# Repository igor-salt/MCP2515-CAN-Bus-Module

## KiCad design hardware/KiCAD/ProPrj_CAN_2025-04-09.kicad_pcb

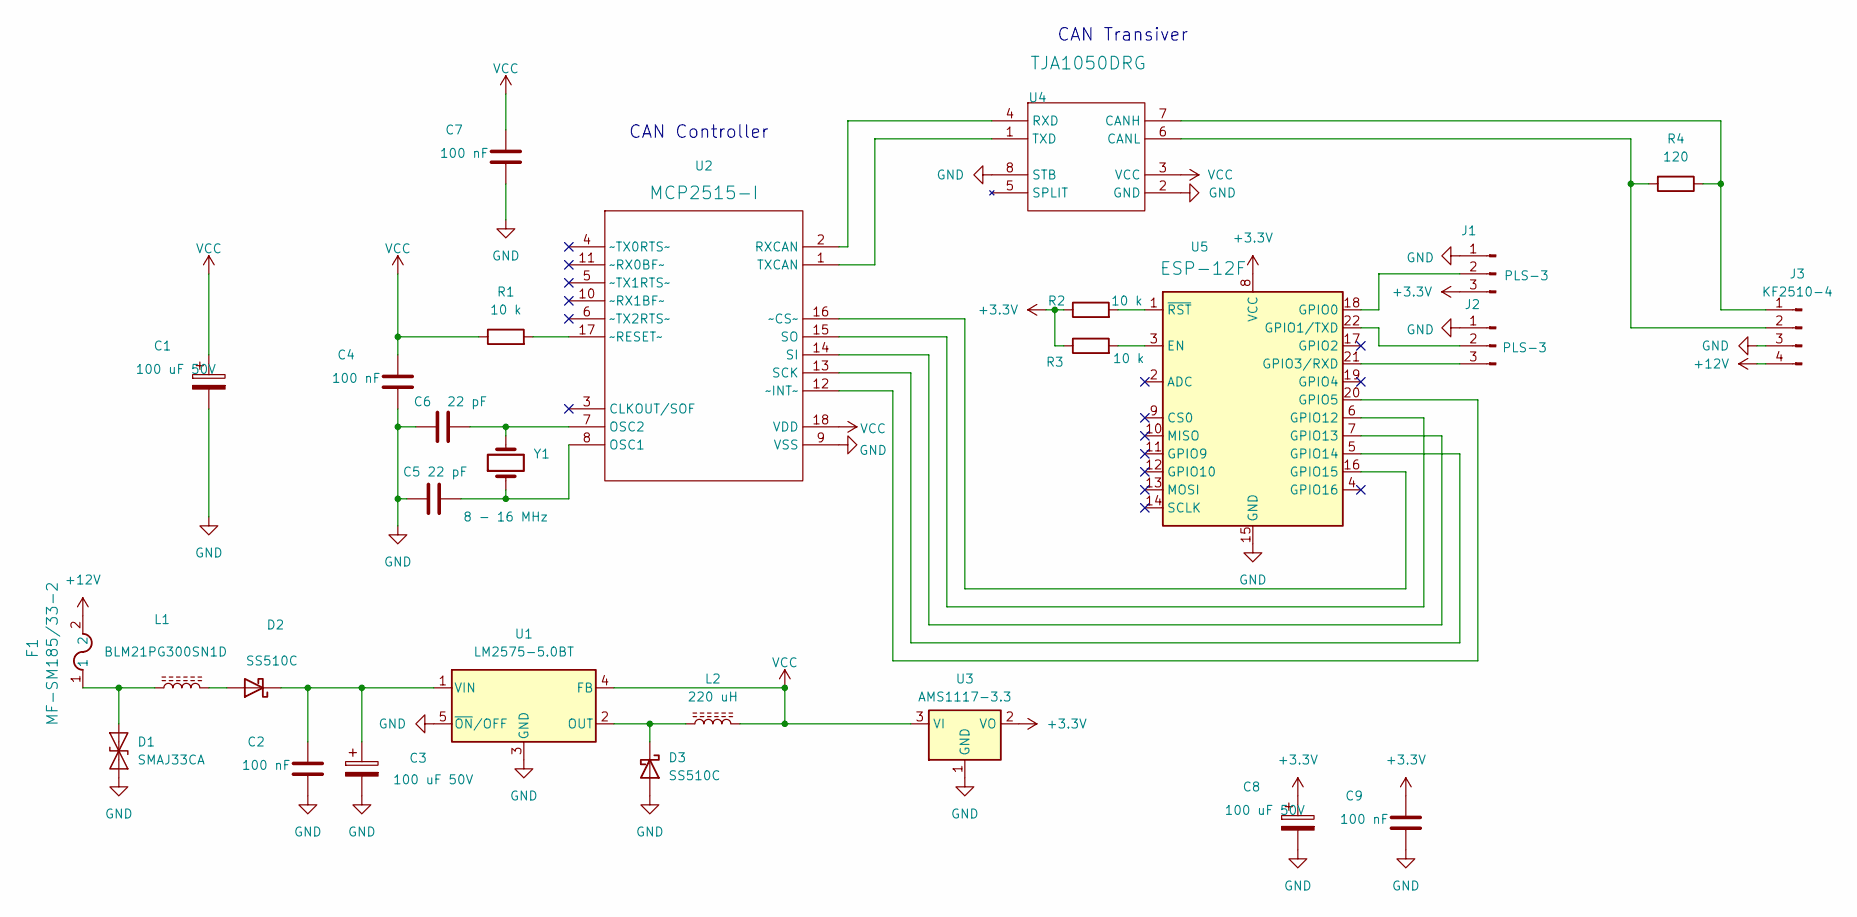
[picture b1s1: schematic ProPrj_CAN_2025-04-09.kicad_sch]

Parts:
C1, C3, C8: 100 uF 50V; C_Elec_8x10.2
C2, C4, C7, C9: 100 nF; C_0603_1608Metric_Pad1.08x0.95mm_HandSolder
C5, C6: 22 pF; C_0603_1608Metric_Pad1.08x0.95mm_HandSolder
D1: SMAJ33CA; D_SMB-SMC_Universal_Handsoldering
D2, D3: SS510C; D_SMB-SMC_Universal_Handsoldering
F1: MF-SM185/33-2; FUSE_MF-SM185_BRN
J1, J2: PLS-3; PinHeader_1x03_P2.54mm_Vertical
J3: KF2510-4; Molex_KK-254_AE-6410-04A_1x04_P2.54mm_Vertical
L1: BLM21PG300SN1D; L_0805_2012Metric_Pad1.05x1.20mm_HandSolder
L2: 220 uH; L_12x12_universal
R1, R2, R3: 10 k; R_0603_1608Metric_Pad0.98x0.95mm_HandSolder
R4: 120; R_0603_1608Metric_Pad0.98x0.95mm_HandSolder
U1: LM2575-5.0BT; TO-263-5_TabPin3
U2: MCP2515-I; SOIC-18_L11.6-W7.5-P1.27-LS10.3-BL; Manufacturer Part MCP2515-I; LCSC Part Name CAN芯片
U3: AMS1117-3.3; SOT-223-3_TabPin2
U4: TJA1050DRG; SOIC-8E; Manufacturer Part TJA1050DRG; LCSC Part Name TJA1050DRG
U5: ESP-12F; ESP-12E
Y1: 8 - 16 MHz; Crystal_SMD_THT_HC49_HandSoldering

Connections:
+3.3V: C8.1, C9.1, J1.3, R2.1, R3.1, U3.2 (VO), U5.8 (VCC)
+12V: F1.2, J3.4
GND: C1.2, C2.2, C3.2, C4.2, C5.1, C6.1, C7.2, C8.2, C9.2, D1.1 (A1), D3.2 (A), J1.1, J2.1, J3.3, U1.3 (GND), U1.5 (~ON/OFF), U2.9 (VSS), U3.1 (GND), U4.2 (GND), U4.8 (STB), U5.15 (GND)
unnamed: D1.2 (A2), F1.1, L1.1
unnamed: D2.2 (A), L1.2
unnamed: C2.1, C3.1, D2.1 (K), U1.1 (VIN)
unnamed: D3.1 (K), L2.1, U1.2 (OUT)
unnamed: J1.2, U5.18 (GPIO0)
unnamed: J2.2, U5.22 (GPIO1/TXD)
unnamed: J2.3, U5.21 (GPIO3/RXD)
unnamed: J3.1, R4.1, U4.7 (CANH)
unnamed: J3.2, R4.2, U4.6 (CANL)
unnamed: C5.2, U2.8 (OSC1), Y1.1
unnamed: C6.2, U2.7 (OSC2), Y1.2
unnamed: U2.2 (RXCAN), U4.4 (RXD)
unnamed: U2.13 (SCK), U5.5 (GPIO14)
unnamed: U2.14 (SI), U5.7 (GPIO13)
unnamed: U2.15 (SO), U5.6 (GPIO12)
unnamed: U2.1 (TXCAN), U4.1 (TXD)
unnamed: U2.16 (~CS~), U5.16 (GPIO15)
unnamed: U2.12 (~INT~), U5.20 (GPIO5)
unnamed: R1.2, U2.17 (~RESET~)
unnamed: R3.2, U5.3 (EN)
unnamed: R2.2, U5.1 (~RST)
VCC: C1.1, C4.1, C7.1, L2.2, R1.1, U1.4 (FB), U2.18 (VDD), U3.3 (VI), U4.3 (VCC)

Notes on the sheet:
CAN Controller
CAN Transiver

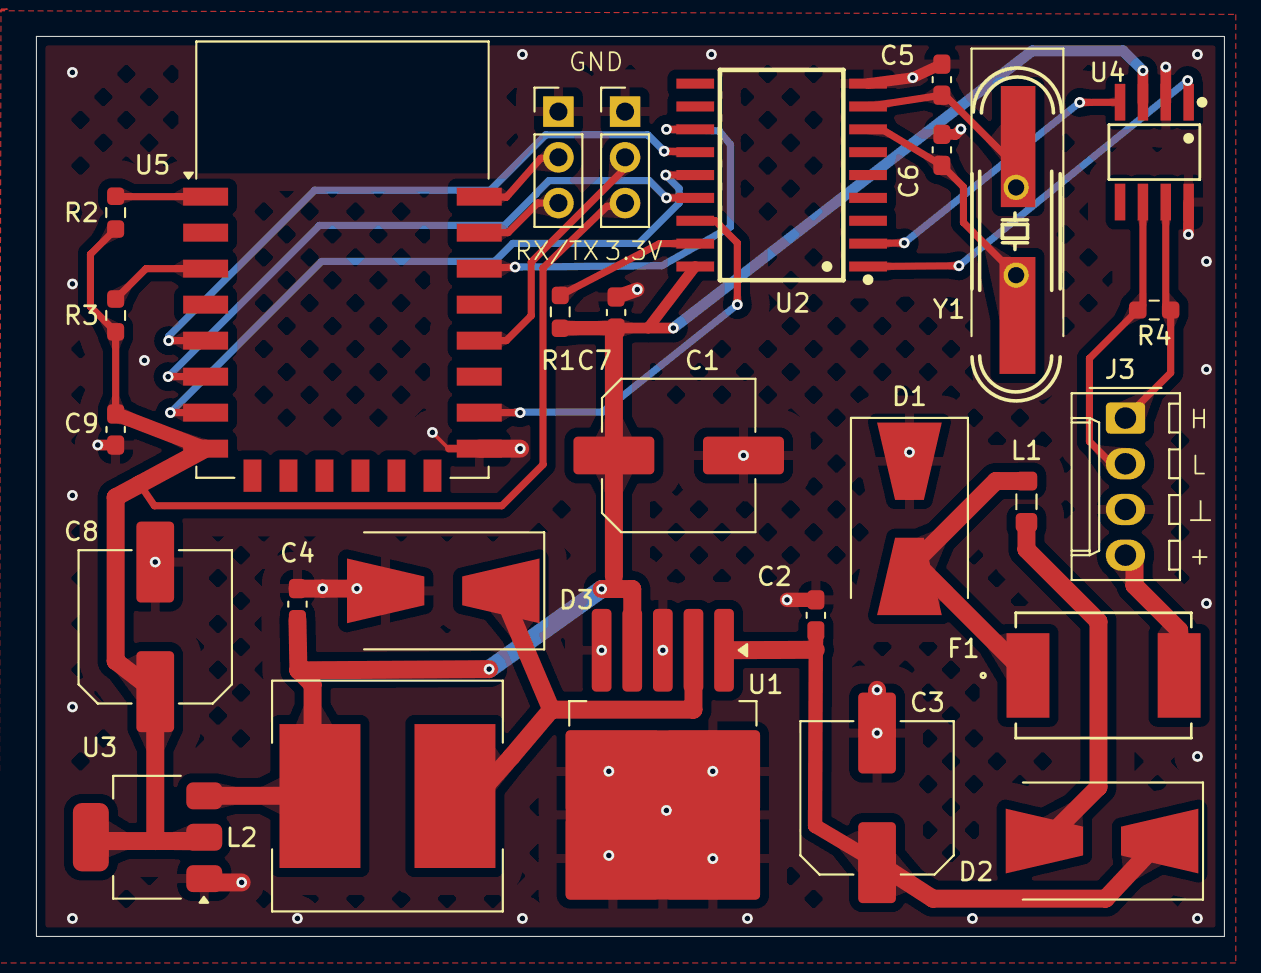
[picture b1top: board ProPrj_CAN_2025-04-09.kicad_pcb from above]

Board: 2 copper layers, 66.0 x 50.0 mm, 28 parts (0 on the bottom side), 25 nets.

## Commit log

2025-04-09 add ASCII
2025-04-09 add KiCAD project
2025-04-09 edit
2025-04-10 reorder
2025-04-11 Rouring
2025-05-06 done
